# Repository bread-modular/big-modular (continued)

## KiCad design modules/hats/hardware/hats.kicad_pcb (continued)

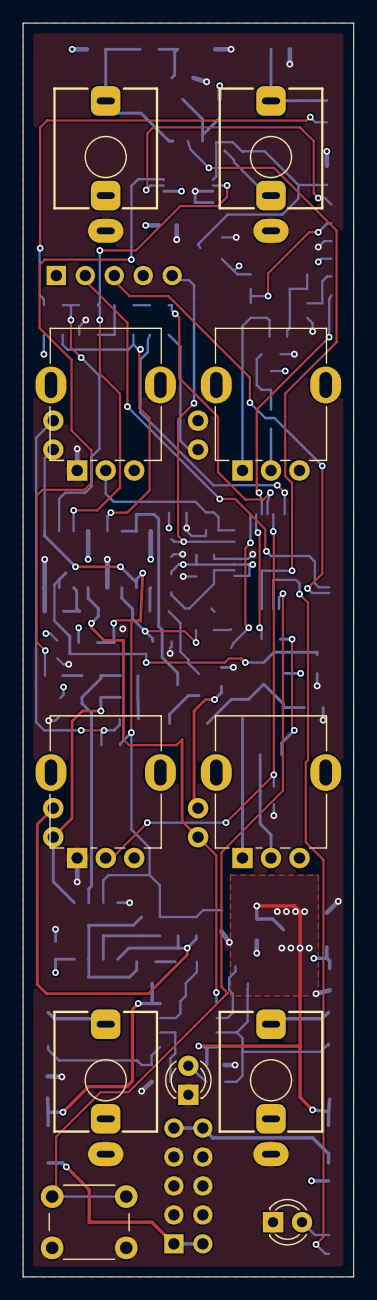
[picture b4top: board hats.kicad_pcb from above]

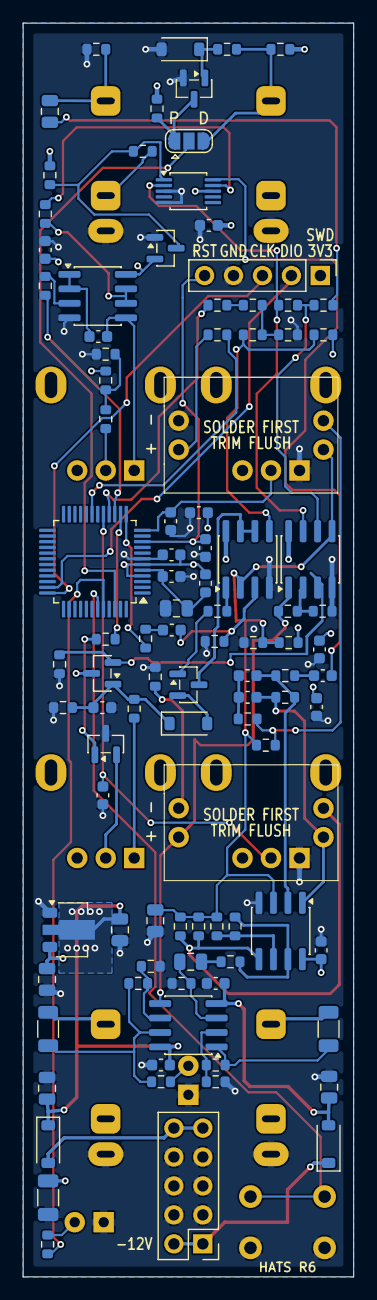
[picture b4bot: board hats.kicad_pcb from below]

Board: 4 copper layers, 29.0 x 110.0 mm, 111 parts (100 on the bottom side), 74 nets.

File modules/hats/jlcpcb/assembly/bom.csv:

Comment,Designator,Footprint,LCSC Part #,Quantity,Manufacturer,MPN
10u,"C1, C2, C4",C_0805_2012Metric,C15850,3,Samsung,CL21A106KAYNNNE
1u,"C3, C10, C21, C24",C_0805_2012Metric,C28323,4,Samsung,CL21B105KBFNNNE
100u,C5,C_1206_3216Metric,C15008,1,Samsung,CL31A107MQHNNNE
100n,"C6, C9, C11, C16, C19, C20, C22, C23, C25, C26",C_0603_1608Metric,C14663,10,YAGEO,CC0603KRX7R9BB104
4.7u,"C7, C18",C_0603_1608Metric,C19666,2,Samsung,CL10A475KO8NNNC
100p,"C8, C12",C_0603_1608Metric,C14858,2,Samsung,CL10C101JB8NNNC
1n,"C13, C14",C_0603_1608Metric,C1588,2,Samsung,CL10B102KB8NNNC
47u,C15,C_0805_2012Metric,C16780,1,Samsung,CL21A476MQYNNNE
10n,"C17, C27, C28",C_0603_1608Metric,C57112,3,FH (Guangdong Fenghua),0603B103K500NT
B5819W,"D1, D2, D4",D_SOD-123,C8598,3,CJ (Jiangsu Changjing),B5819W SL
1N4148W,D3,D_SOD-123,C81598,1,ST(Semtech),1N4148W
BAV199,D7,SOT-23,C40919,1,Nexperia,"BAV199,215"
600R@100MHz,FB1,L_0603_1608Metric,C1002,1,Sunlord,GZ1608D601TF
MMBT3904,Q1,SOT-23,C20526,1,CJ (Jiangsu Changjing),MMBT3904(RANGE:100-300)
SS8050,"Q2, Q4",SOT-23,C431710,2,MDD(Microdiode Semiconductor),SS8050
SS8550,Q3,SOT-23,C364314,1,MDD(Microdiode Semiconductor),SS8550
100k,"R1, R11, R12, R15, R27, R30, R31, R38, R39, R40, R45",R_0603_1608Metric,C25803,11,UNI-ROYAL,0603WAF1003T5E
10k,"R2, R21, R26, R29, R37, R42",R_0603_1608Metric,C25804,6,UNI-ROYAL,0603WAF1002T5E
22k,"R3, R20, R34, R49",R_0603_1608Metric,C31850,4,UNI-ROYAL,0603WAF2202T5E
1k,"R6, R8, R9, R10, R17, R22, R24, R25, R47, R48",R_0603_1608Metric,C21190,10,UNI-ROYAL,0603WAF1001T5E
330,"R7, R18, R19, R23, R28, R35, R51",R_0603_1608Metric,C23138,7,UNI-ROYAL,0603WAF3300T5E
33k,R13,R_0603_1608Metric,C4216,1,UNI-ROYAL,0603WAF3302T5E
470k,R14,R_0603_1608Metric,C23178,1,UNI-ROYAL,0603WAF4703T5E
200k,"R16, R36",R_0603_1608Metric,C25811,2,UNI-ROYAL,0603WAF2003T5E
1M,"R32, R33",R_0603_1608Metric,C22935,2,UNI-ROYAL,0603WAF1004T5E
20k,R41,R_0603_1608Metric,C4184,1,UNI-ROYAL,0603WAF2002T5E
1k,"R43, R46",R_1206_3216Metric,C2074262,2,ROHM,ESR18EZPF1001
51k,"R44, R50",R_0603_1608Metric,C23196,2,UNI-ROYAL,0603WAF5102T5E
HT7533-1,U1,SOT-89-3,C14289,1,Holtek,HT7533-1
STM32G071C8T6,U2,LQFP-48_7x7mm_P0.5mm,C529341,1,STMicroelectronics,STM32G071C8T6
MCP6002,"U4, U6, U8, U9",SOIC-8_3.9x4.9mm_P1.27mm,C7377,4,Microchip,MCP6002T-I/SN
TS5A23157,U5,TSSOP-10_3x3mm_P0.5mm,C11133,1,Texas Instruments,TS5A23157DGSR
TL072,U10,SOIC-8_3.9x4.9mm_P1.27mm,C6961,1,STMicroelectronics,TL072CDT

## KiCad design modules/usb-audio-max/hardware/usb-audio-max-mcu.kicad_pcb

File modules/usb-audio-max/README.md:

# USB-AUDIO-MAX — 6 in / 8 out USB audio interface, 96 kHz, DC coupled

A Eurorack USB audio interface: a CH32V307 (USB 2.0 High-Speed, USB Audio Class 2) and a TI
PCM3168A 24-bit codec in TDM mode. Six inputs and eight outputs, all DC coupled at about +/-5.9 V,
so CV works too. No level controls. Same two-board build as [USB-AUDIO](../usb-audio/README.md).

| Panel | Circuit |
|---|---|
| **USB** (USB-C through the panel) | MCU board: CH32V307RCT6, USBLC6-2SC6, data only (powered from the rack) |
| **IN 1-6** | 100k -> inverting driver on +5 V (x -0.24) -> PCM3168A VIN+ (single-ended); +/-5.89 V = full scale |
| **OUT 1-8** | PCM3168A VOUT+/- -> difference amplifier on +/-12 V (x 1.467) -> 1k; full scale +/-5.87 V |
| (DC reference) | +5 V analog = the codec's full-scale reference: REF5050 (8 ppm/C) -> LM358 + BCP56 discrete regulator (current-limited), so calibrated CV levels don't drift |
| (+3.3 V digital) | TPS562208 buck in forced-continuous mode (~580 kHz at every load, never in the audio band) behind a 2.2R + ferrite input filter, molded inductor; only the digital rail switches (+12 V ~0.34 A max). ngspice: ~50 uV on +12 V, 0.1 uV on +5 V analog, -142 dBFS at the jacks for USB load bursts |

**Status: S2 schematics + R1 routing on both boards, fab-review fixes done (2026-11-08), JLCPCB
export in `jlcpcb/` (not supplier-accepted, not built).** 10HP panel: USB-C at the top, then IN 1-6 in
two rows of three and OUT 1-8 in three rows (the ninth spot, bottom right, is empty; the power header sits
behind it). Both boards: native ERC 0, DRC 0 (saved fills too), unconnected 0, parity 0. Ten R/C
placements are JLCPCB Extended (user decision open, `jlcpcb/README.md`); no firmware yet (96 kHz SPI1
path untested). JLC stocks the PCM3168APAPR (C529289, Extended, 1517 on 2026-11-08).

| Path | Contents |
|---|---|
| `hardware/` | `usb-audio-max.kicad_{pro,sch,pcb}` (carrier), `usb-audio-max-mcu.kicad_{pro,sch,pcb}` (MCU board), shared `USBAUDIOMAX.kicad_sym`, `USBAUDIOMAX.pretty` (+ `PROVENANCE.json`), `USBAUDIOMAX.3dshapes`, vendored 3D models `_kicad_models/` |
| `jlcpcb/` | JLCPCB sets: `main/` (carrier Gerbers + bottom BOM/CPL, panel Gerbers), `mcu/` (MCU board Gerbers + top BOM/CPL); upload map and parts audit in `jlcpcb/README.md` |
| `panels/front-pcb/` | 10HP FR4 panel `usb-audio-max-panel.kicad_{pro,pcb}` (NPTH holes, USB-C slot, labels) |
| `docs/research.md` | Brief, decisions, levels, buck-vs-audio simulation, circuit, TDM/firmware notes, panel and fit study, sourcing, open items |
| `docs/geometry.json` | Placement and stack contract (panel frame) |
| `docs/*-schematic.pdf`, `docs/erc/`, `docs/fit/` | Schematic PDFs, native ERC JSON, native DRC JSON and placement renders |
| `tools/` | Generators (`circuit_carrier.py`, `circuit_mcu.py` hold the circuits; `build_layout.py` the S1 boards), checks, `kicad-project*.json` profiles |

Rebuild (from `modules/usb-audio-max`):

```sh
python3 -B tools/import_footprints.py   # footprint library (pcbnew); reads the Bread Modular AudioJacks/K2
python3 -B tools/build_schematic.py     # both schematics + pinned symbols, netlists asserted
python3 -B tools/build_project.py       # .kicad_pro files (only before hand edits)
python3 -B tools/build_layout.py        # S1 boards + panel (only before hand placement starts)
python3 -B tools/check_edges.py         # courtyards >= 1 mm from the edges, SMD >= 2 mm from jack pads
python3 -B tools/fit_density.py         # fit study (docs/research.md section 5)
python3 -B tools/render_fit.py          # docs/fit/*.png
kicad-cli sch erc --severity-all --format json -o docs/erc/carrier-erc.json hardware/usb-audio-max.kicad_sch
kicad-cli sch erc --severity-all --format json -o docs/erc/mcu-erc.json hardware/usb-audio-max-mcu.kicad_sch
kicad-cli pcb drc --severity-all --schematic-parity --refill-zones --format json -o docs/fit/carrier-drc.json hardware/usb-audio-max.kicad_pcb
kicad-cli pcb drc --severity-all --schematic-parity --refill-zones --format json -o docs/fit/mcu-drc.json hardware/usb-audio-max-mcu.kicad_pcb
```

Shared gate (from the repository root): `python3 -B opt/kicad-tools/kicad_tools.py check --config
modules/usb-audio-max/tools/kicad-project.json --reports <new-dir>` (and `kicad-project-mcu.json`).

Read [`Code.md`](Code.md) before changing hardware.

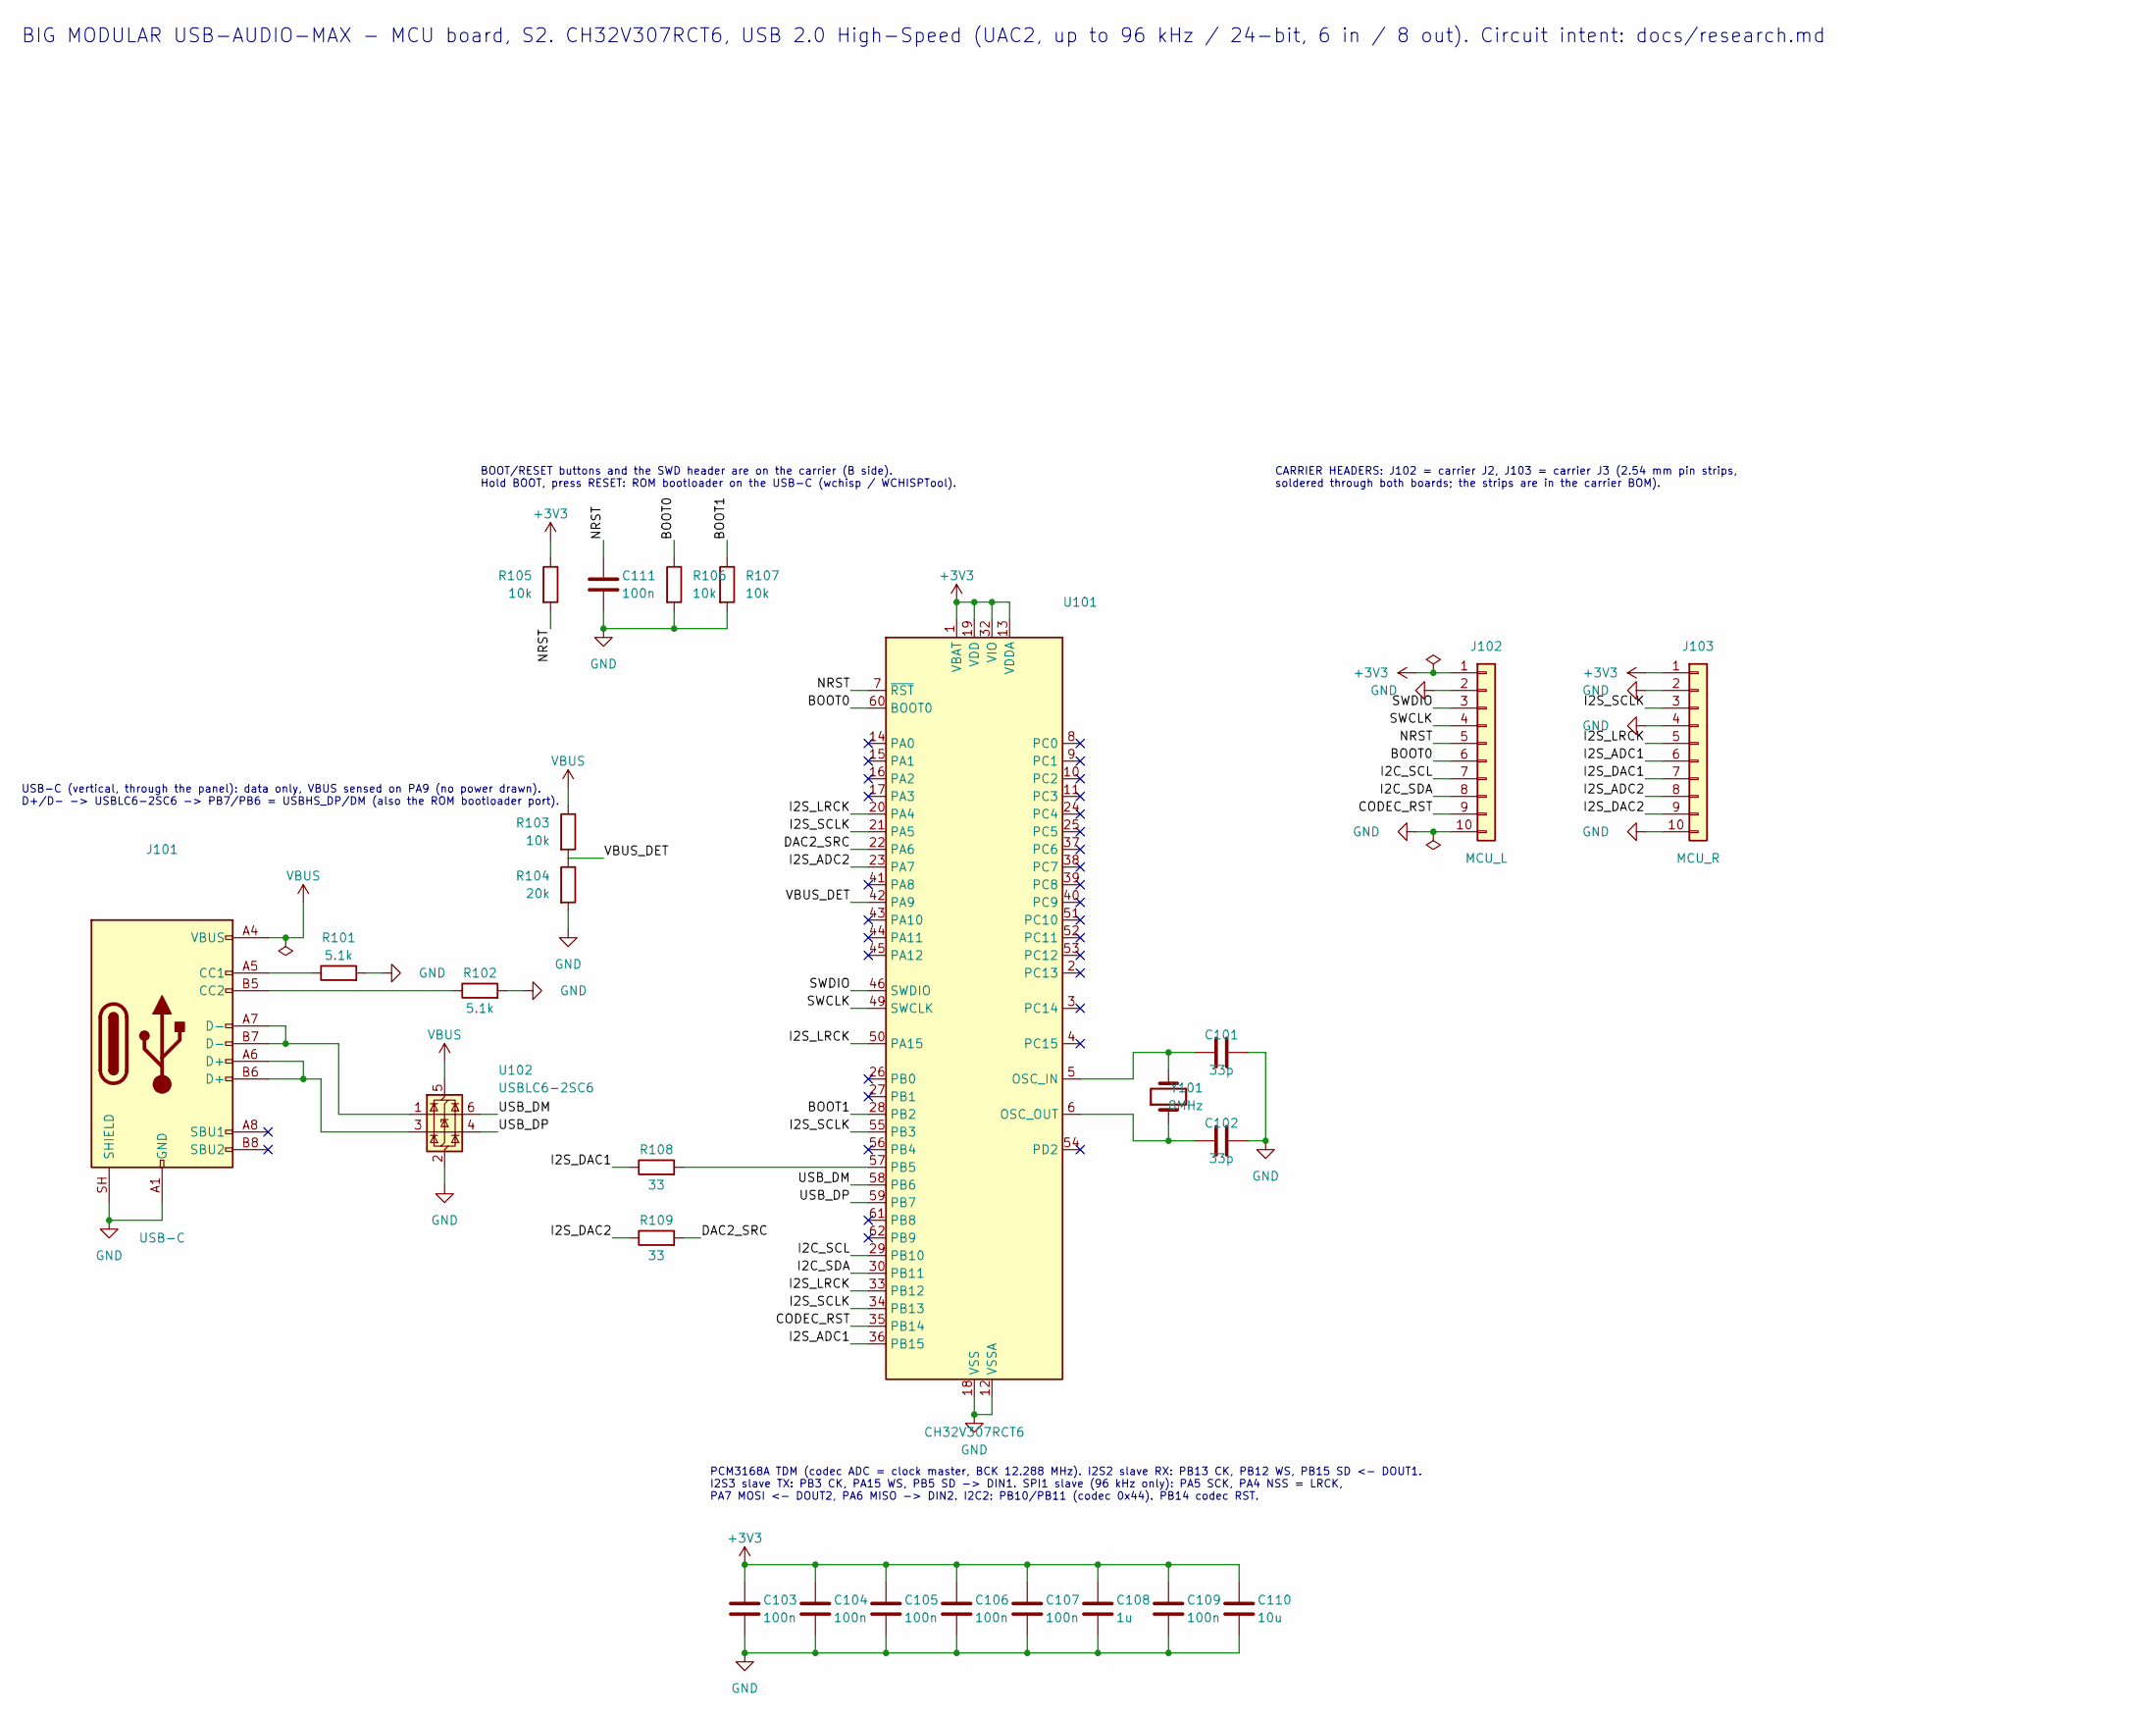
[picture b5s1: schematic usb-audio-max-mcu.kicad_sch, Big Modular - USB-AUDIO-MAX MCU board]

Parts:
C101, C102: 33p; C_0402_1005Metric; Voltage 50V; MPN 0402CG330J500NT; LCSC C1562
C103, C104, C105, C106, C107, C109, C111: 100n; C_0402_1005Metric; Voltage 16V; MPN CL05B104KO5NNNC; LCSC C1525
C108: 1u; C_0402_1005Metric; Voltage 25V; MPN CL05A105KA5NQNC; LCSC C52923
C110: 10u; C_0603_1608Metric; Voltage 10V; MPN CL10A106KP8NNNC; LCSC C19702
J101: USB-C; USB_C_Receptacle_HRO_TYPE-C-31-D-15_Vertical; MPN TYPE-C-31-D-15; LCSC C22464480
J102: MCU_L; PinHeader_1x10_P2.54mm_Vertical
J103: MCU_R; PinHeader_1x10_P2.54mm_Vertical
R101, R102: 5.1k; R_0402_1005Metric; MPN 0402WGF5101TCE; LCSC C25905
R103, R105, R106, R107: 10k; R_0402_1005Metric; MPN 0402WGF1002TCE; LCSC C25744
R104: 20k; R_0402_1005Metric; MPN 0402WGF2002TCE; LCSC C25765
R108, R109: 33; R_0402_1005Metric; MPN 0402WGF330JTCE; LCSC C25105
U101: CH32V307RCT6; LQFP-64_10x10mm_P0.5mm; MPN CH32V307RCT6; LCSC C2988083
U102: USBLC6-2SC6; SOT-23-6; MPN USBLC6-2SC6; LCSC C7519
Y101: 8MHz; Crystal_SMD_5032-2Pin_5.0x3.2mm; MPN X50328MSB2GI; LCSC C115962

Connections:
+3V3: C103.1, C104.1, C105.1, C106.1, C107.1, C108.1, C109.1, C110.1, J102.1, J103.1, R105.1, U101.1 (VBAT), U101.13 (VDDA), U101.19 (VDD), U101.32 (VIO), U101.48 (VDD), U101.64 (VIO)
/BOOT0: J102.6, R106.1, U101.60 (BOOT0)
/BOOT1: R107.1, U101.28 (PB2)
/CODEC_RST: J102.9, U101.35 (PB14)
/DAC2_SRC: R109.2, U101.22 (PA6)
/I2C_SCL: J102.7, U101.29 (PB10)
/I2C_SDA: J102.8, U101.30 (PB11)
/I2S_ADC1: J103.6, U101.36 (PB15)
/I2S_ADC2: J103.8, U101.23 (PA7)
/I2S_DAC1: J103.7, R108.1
/I2S_DAC2: J103.9, R109.1
/I2S_LRCK: J103.5, U101.20 (PA4), U101.33 (PB12), U101.50 (PA15)
/I2S_SCLK: J103.3, U101.21 (PA5), U101.34 (PB13), U101.55 (PB3)
/NRST: C111.1, J102.5, R105.2, U101.7 (~RST)
/SWCLK: J102.4, U101.49 (SWCLK)
/SWDIO: J102.3, U101.46 (SWDIO)
/USB_DM: U101.58 (PB6), U102.6 (I/O1)
/USB_DP: U101.59 (PB7), U102.4 (I/O2)
/VBUS_DET: R103.2, R104.1, U101.42 (PA9)
GND: C101.2, C102.2, C103.2, C104.2, C105.2, C106.2, C107.2, C108.2, C109.2, C110.2, C111.2, J101.A1 (GND), J101.A12 (GND), J101.B1 (GND), J101.B12 (GND), J101.SH (SHIELD), J102.2, J102.10, J103.2, J103.4, J103.10, R101.2, R102.2, R104.2, R106.2, R107.2, U101.12 (VSSA), U101.18 (VSS), U101.31 (VSS), U101.47 (VSS), U101.63 (VSS), U102.2 (GND)
unnamed: J101.A5 (CC1), R101.1
unnamed: J101.B5 (CC2), R102.1
unnamed: J101.A6 (D+), J101.B6 (D+), U102.3 (I/O2)
unnamed: J101.A7 (D-), J101.B7 (D-), U102.1 (I/O1)
unnamed: C101.1, U101.5 (OSC_IN), Y101.2
unnamed: C102.1, U101.6 (OSC_OUT), Y101.1
unnamed: R108.2, U101.57 (PB5)
VBUS: J101.A4 (VBUS), J101.A9 (VBUS), J101.B4 (VBUS), J101.B9 (VBUS), R103.1, U102.5 (VBUS)

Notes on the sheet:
CARRIER HEADERS: J102 = carrier J2, J103 = carrier J3 (2.54 mm pin strips, soldered through both boards; the strips are in the carrier BOM).
BOOT/RESET buttons and the SWD header are on the carrier (B side). Hold BOOT, press RESET: ROM bootloader on the USB-C (wchisp / WCHISPTool).
PCM3168A TDM (codec ADC = clock master, BCK 12.288 MHz). I2S2 slave RX: PB13 CK, PB12 WS, PB15 SD <- DOUT1. I2S3 slave TX: PB3 CK, PA15 WS, PB5 SD -> DIN1. SPI1 slave (96 kHz only): PA5 SCK, PA4 NSS = LRCK, PA7 MOSI <- DOUT2, PA6 MISO -> DIN2. I2C2: PB10/PB11 (codec 0x44). PB14 codec RST.
BIG MODULAR USB-AUDIO-MAX - MCU board, S2. CH32V307RCT6, USB 2.0 High-Speed (UAC2, up to 96 kHz / 24-bit, 6 in / 8 out). Circuit intent: docs/research.md
USB-C (vertical, through the panel): data only, VBUS sensed on PA9 (no power drawn). D+/D- -> USBLC6-2SC6 -> PB7/PB6 = USBHS_DP/DM (also the ROM bootloader port).

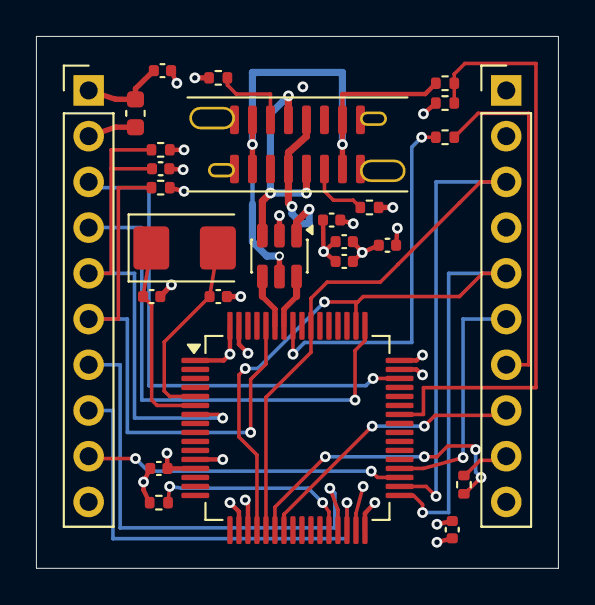
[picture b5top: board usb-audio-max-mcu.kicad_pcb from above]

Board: 4 copper layers, 29.0 x 29.5 mm, 26 parts (0 on the bottom side), 28 nets.

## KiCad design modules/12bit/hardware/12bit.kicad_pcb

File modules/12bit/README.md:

# 12bit — STM32G071 two-channel DAC voice (6HP)

modules/8bit moved from the ATtiny1616 to an **STM32G071C8T6**: its two 12-bit DAC channels
drive two outputs and the passive low-pass is gone (knob 3 is a plain knob). 6HP. (The S1
gate output was removed in S2.)

| Panel (top to bottom) | Circuit |
|---|---|
| **MIDI** in (TS) / **CV** in | 8bit MIDI V2 NPN front end, JP1 on the back (shipped open): `P` = protected (USART1 RX inverted in firmware), `D` = direct. CV: -5.9..+6.0 V -> 0..3.3 V (Zin 138k), BAT54SW clamp, MCP6001 follower into PA0; unpatched = 0 V |
| **P1**, **P2** / **MODE**, LED, **P3** | 50k linear RV09 dividers into PA1 / PA6 / PA7. MODE: 8bit 6 x 6 x 7 mm THT switch (PB4) with the 8bit printed cap; 3 mm LED beside it on the same row (PB5, PWM) |
| **OUT 1**, **OUT 2** | DAC1_OUT1 / DAC1_OUT2 -> 1k/4.7n step smoothing (34 kHz) -> TL074 x3.4 around a 2.33 V offset -> ±4.9 V, DC coupled (audio, CV or LFO), 1k 0.5 W |

Power: Eurorack 10-pin (16-pin IDC fits) on B, upright at the right edge above OUT 2, ±12 V through series
Schottkys, +3V3 from an HT7533-1. SWD on a 1x5 header on B (1 3V3 sense, 2 SWDIO, 3 SWCLK,
4 GND, 5 NRST).

**Status: S2 schematic (ERC 0) + P3 placement + R2 2-layer hand routing (DRC 0, unconnected 0,
parity 0) + JLCPCB export in `jlcpcb/` (not supplier-accepted).** No firmware. See `docs/research.md` for decisions and open items.

| Path | Contents |
|---|---|
| `hardware/` | KiCad project `12bit.kicad_{pro,sch,pcb}` (29 x 110 mm carrier, 2 layers, routed R2), pinned symbols/footprints/models |
| `panels/front-pcb/12bit-panel.kicad_{pro,pcb}` | 6HP FR4 front panel: NPTH only, silkscreen labels |
| `docs/research.md` | Brief, decisions, circuit, placement, open items |
| `docs/geometry.json` | Placement contract (panel frame) |
| `docs/12bit-schematic.pdf`, `docs/fit/` | Schematic PDF; native ERC/DRC JSON and renders |
| `docs/schematic-symbols.json`, `docs/sourcing-candidates.json` | Pinned-symbol provenance; dated live JLCPCB lookups |
| `tools/` | Generators and the shared-tool profile `kicad-project.json` |

Rebuild (from `modules/12bit`; the carrier is now routed, so `build_layout.py` refuses it; use `--panel-only` for the panel):

```sh
python3 -B tools/import_footprints.py   # one-time library import (pcbnew)
python3 -B tools/build_schematic.py     # schematic + pinned symbols, netlist asserted
python3 -B tools/build_layout.py        # THT placement + parked SMD + nets, UNROUTED; panel
(cd ../.. && python3 -B opt/kicad-tools/kicad_tools.py check --config modules/12bit/tools/kicad-project.json \
   --reports modules/12bit/research/check-NEW)
```

Read [`Code.md`](Code.md) before changing hardware.

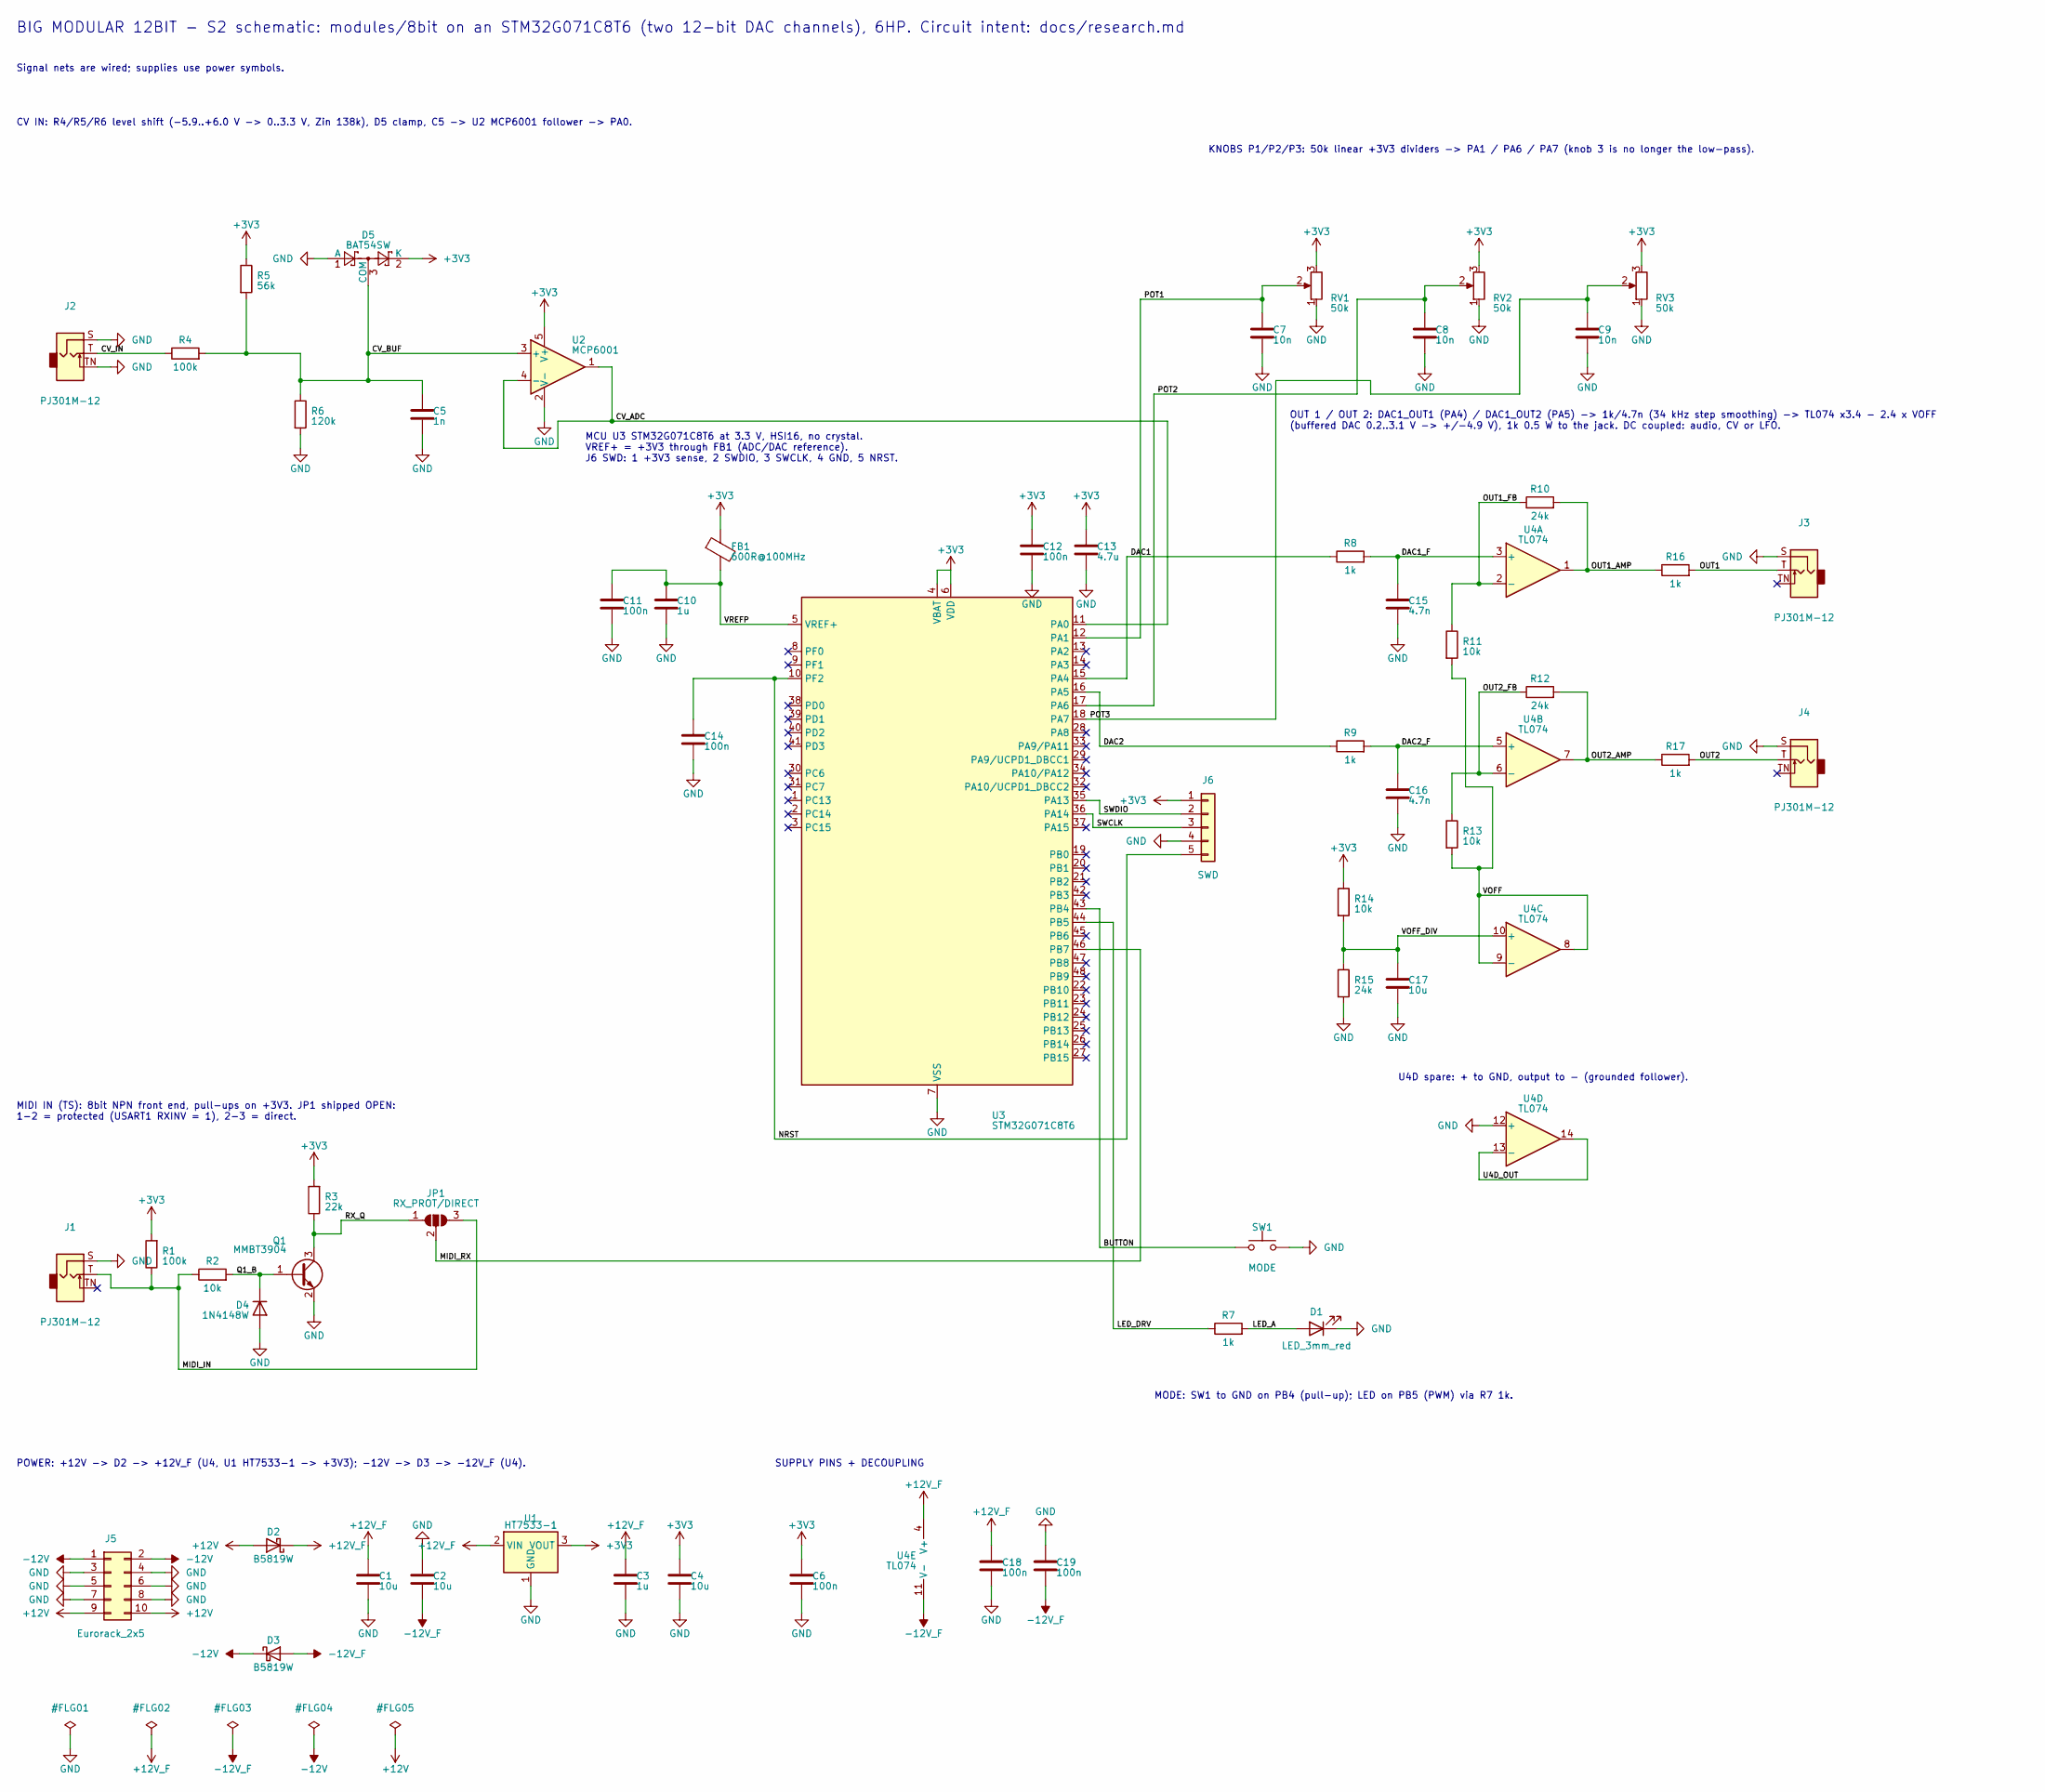
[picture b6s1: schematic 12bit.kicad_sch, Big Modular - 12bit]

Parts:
C1, C2, C4, C17: 10u; C_0805_2012Metric; Voltage 25V; MPN CL21A106KAYNNNE; LCSC C15850
C3, C10: 1u; C_0805_2012Metric; Voltage 50V; MPN CL21B105KBFNNNE; LCSC C28323
C5: 1n; C_0603_1608Metric; Voltage 50V; MPN CL10B102KB8NNNC; LCSC C1588
C6, C11, C12, C14, C18, C19: 100n; C_0603_1608Metric; Voltage 50V; MPN CC0603KRX7R9BB104; LCSC C14663
C7, C8, C9: 10n; C_0603_1608Metric; Voltage 50V; MPN 0603B103K500NT; LCSC C57112
C13: 4.7u; C_0603_1608Metric; Voltage 16V; MPN CL10A475KO8NNNC; LCSC C19666
C15, C16: 4.7n; C_0603_1608Metric; Voltage 50V; MPN 0603B472K500NT; LCSC C53987
D1: LED_3mm_red; LED_D3.0mm
D2, D3: B5819W; D_SOD-123; MPN B5819W SL; LCSC C8598
D4: 1N4148W; D_SOD-123; MPN 1N4148W; LCSC C81598
D5: BAT54SW; SOT-323_SC-70; MPN BAT54SWT1G; LCSC C78260
FB1: 600R@100MHz; L_0603_1608Metric; MPN GZ1608D601TF; LCSC C1002
J1, J2, J3, J4: PJ301M-12; Jack_3.5mm_QingPu_WQP-PJ301M-12_Vertical
J5: Eurorack_2x5; PinHeader_2x05_P2.54mm_Vertical
J6: SWD; PinHeader_1x05_P2.54mm_Vertical
JP1: RX_PROT/DIRECT; SolderJumper-3_P1.3mm_Open_RoundedPad1.0x1.5mm
Q1: MMBT3904; SOT-23; MPN MMBT3904(RANGE:100-300); LCSC C20526
R1, R4: 100k; R_0603_1608Metric; MPN 0603WAF1003T5E; LCSC C25803
R2, R11, R13, R14: 10k; R_0603_1608Metric; MPN 0603WAF1002T5E; LCSC C25804
R3: 22k; R_0603_1608Metric; MPN 0603WAF2202T5E; LCSC C31850
R5: 56k; R_0603_1608Metric; MPN 0603WAF5602T5E; LCSC C23206
R6: 120k; R_0603_1608Metric; MPN 0603WAF1203T5E; LCSC C25808
R7, R8, R9: 1k; R_0603_1608Metric; MPN 0603WAF1001T5E; LCSC C21190
R10, R12, R15: 24k; R_0603_1608Metric; MPN 0603WAF2402T5E; LCSC C23352
R16, R17: 1k; R_1206_3216Metric; MPN ESR18EZPF1001; LCSC C2074262
RV1, RV2, RV3: 50k; Potentiometer_RV09
SW1: MODE; SW_PUSH_6mm_H7.3mm; MPN 6x6x7 mm THT tact switch, 4 pins (gener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
U1: HT7533-1; SOT-89-3; MPN HT7533-1; LCSC C14289
U2: MCP6001; SOT-23-5; MPN MCP6001T-E/OT; LCSC C29429
U3: STM32G071C8T6; LQFP-48_7x7mm_P0.5mm; MPN STM32G071C8T6; LCSC C529341
U4: TL074; SOIC-14_3.9x8.7mm_P1.27mm; MPN TL074CDR; LCSC C12594

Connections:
+3V3: C4.1, C6.1, C12.1, C13.1, D5.2 (K), FB1.1, J6.1, R1.2, R3.2, R5.1, R14.1, RV1.3, RV2.3, RV3.3, U1.3 (VOUT), U2.5 (V+), U3.4 (VBAT), U3.6 (VDD)
+12V: D2.2 (A), J5.9, J5.10
+12V_F: C1.1, C3.1, C18.1, D2.1 (K), U1.2 (VIN), U4.4 (V+)
-12V: D3.1 (K), J5.1, J5.2
-12V_F: C2.2, C19.2, D3.2 (A), U4.11 (V-)
/BUTTON: SW1.1, U3.43 (PB4)
/CV_ADC: U2.1, U2.4 (-), U3.11 (PA0)
/CV_BUF: C5.1, D5.3 (COM), R4.2, R5.2, R6.1, U2.3 (+)
/CV_IN: J2.T, R4.1
/DAC1: R8.1, U3.15 (PA4)
/DAC1_F: C15.1, R8.2, U4.3 (+)
/DAC2: R9.1, U3.16 (PA5)
/DAC2_F: C16.1, R9.2, U4.5 (+)
/LED_A: D1.2 (A), R7.2
/LED_DRV: R7.1, U3.44 (PB5)
/MIDI_IN: J1.T, JP1.3 (B), R1.1, R2.1
/MIDI_RX: JP1.2 (C), U3.46 (PB7)
/NRST: C14.1, J6.5, U3.10 (PF2)
/OUT1: J3.T, R16.2
/OUT1_AMP: R10.2, R16.1, U4.1
/OUT1_FB: R10.1, R11.1, U4.2 (-)
/OUT2: J4.T, R17.2
/OUT2_AMP: R12.2, R17.1, U4.7
/OUT2_FB: R12.1, R13.1, U4.6 (-)
/POT1: C7.1, RV1.2, U3.12 (PA1)
/POT2: C8.1, RV2.2, U3.17 (PA6)
/POT3: C9.1, RV3.2, U3.18 (PA7)
/Q1_B: D4.1 (K), Q1.1 (B), R2.2
/RX_Q: JP1.1 (A), Q1.3 (C), R3.1
/SWCLK: J6.3, U3.36 (PA14)
/SWDIO: J6.2, U3.35 (PA13)
/U4D_OUT: U4.13 (-), U4.14
/VOFF: R11.2, R13.2, U4.8, U4.9 (-)
/VOFF_DIV: C17.1, R14.2, R15.1, U4.10 (+)
/VREFP: C10.1, C11.1, FB1.2, U3.5 (VREF+)
GND: C1.2, C2.1, C3.2, C4.2, C5.2, C6.2, C7.2, C8.2, C9.2, C10.2, C11.2, C12.2, C13.2, C14.2, C15.2, C16.2, C17.2, C18.2, C19.1, D1.1 (K), D4.2 (A), D5.1 (A), J1.S, J2.S, J2.TN, J3.S, J4.S, J5.3, J5.4, J5.5, J5.6, J5.7, J5.8, J6.4, Q1.2 (E), R6.2, R15.2, RV1.1, RV2.1, RV3.1, SW1.2, U1.1 (GND), U2.2 (V-), U3.7 (VSS), U4.12 (+)

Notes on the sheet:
SUPPLY PINS + DECOUPLING
CV IN: R4/R5/R6 level shift (-5.9..+6.0 V -> 0..3.3 V, Zin 138k), D5 clamp, C5 -> U2 MCP6001 follower -> PA0.
U4D spare: + to GND, output to - (grounded follower).
Signal nets are wired; supplies use power symbols.
MCU U3 STM32G071C8T6 at 3.3 V, HSI16, no crystal. VREF+ = +3V3 through FB1 (ADC/DAC reference). J6 SWD: 1 +3V3 sense, 2 SWDIO, 3 SWCLK, 4 GND, 5 NRST.
MODE: SW1 to GND on PB4 (pull-up); LED on PB5 (PWM) via R7 1k.
MIDI IN (TS): 8bit NPN front end, pull-ups on +3V3. JP1 shipped OPEN: 1-2 = protected (USART1 RXINV = 1), 2-3 = direct.
BIG MODULAR 12BIT - S2 schematic: modules/8bit on an STM32G071C8T6 (two 12-bit DAC channels), 6HP. Circuit intent: docs/research.md
KNOBS P1/P2/P3: 50k linear +3V3 dividers -> PA1 / PA6 / PA7 (knob 3 is no longer the low-pass).
OUT 1 / OUT 2: DAC1_OUT1 (PA4) / DAC1_OUT2 (PA5) -> 1k/4.7n (34 kHz step smoothing) -> TL074 x3.4 - 2.4 x VOFF (buffered DAC 0.2..3.1 V -> +/-4.9 V), 1k 0.5 W to the jack. DC coupled: audio, CV or LFO.
POWER: +12V -> D2 -> +12V_F (U4, U1 HT7533-1 -> +3V3); -12V -> D3 -> -12V_F (U4).

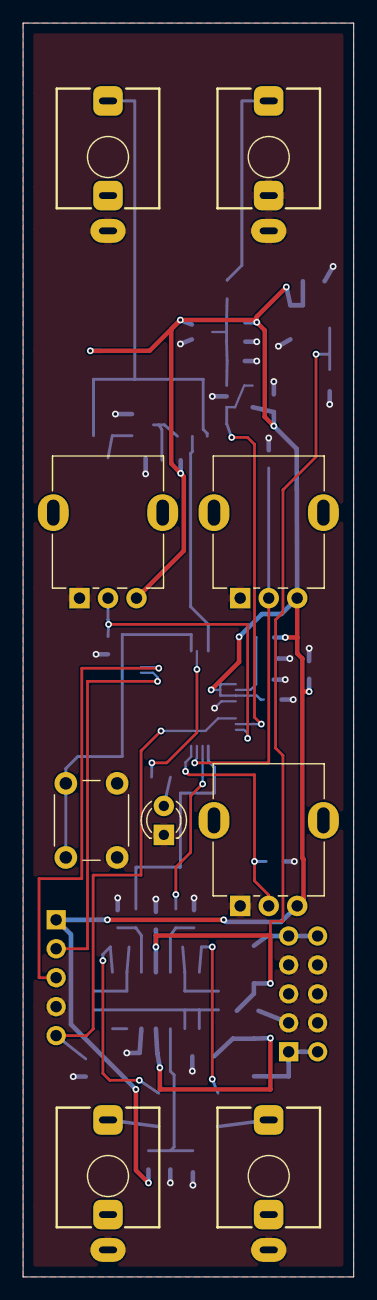
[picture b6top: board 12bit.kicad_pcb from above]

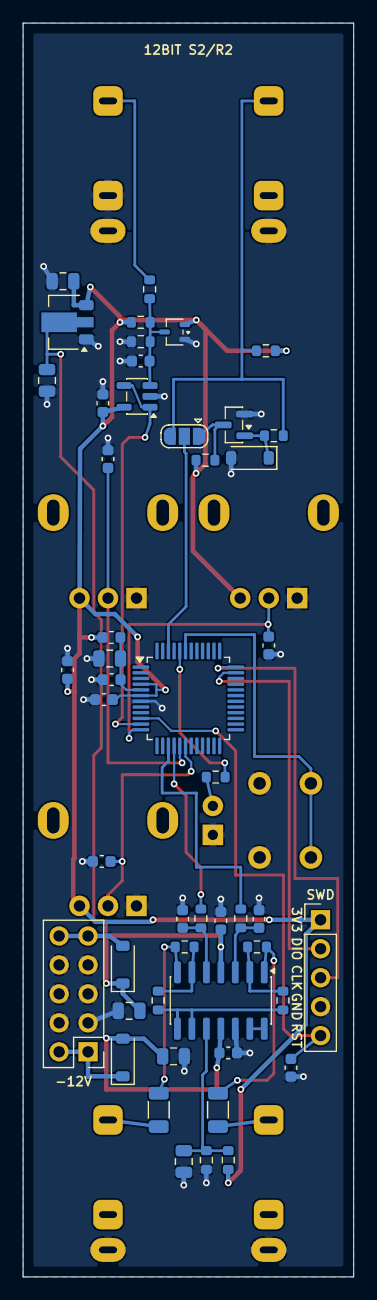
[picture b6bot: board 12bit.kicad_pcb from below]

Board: 2 copper layers, 29.0 x 110.0 mm, 58 parts (49 on the bottom side), 36 nets.

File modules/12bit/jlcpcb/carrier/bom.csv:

Comment,Designator,Footprint,LCSC Part #,Quantity,Manufacturer,MPN
10u,"C1, C2, C4, C17",C_0805_2012Metric,C15850,4,Samsung,CL21A106KAYNNNE
1u,"C3, C10",C_0805_2012Metric,C28323,2,Samsung,CL21B105KBFNNNE
1n,C5,C_0603_1608Metric,C1588,1,Samsung,CL10B102KB8NNNC
100n,"C6, C11, C12, C14, C18, C19",C_0603_1608Metric,C14663,6,YAGEO,CC0603KRX7R9BB104
10n,"C7, C8, C9",C_0603_1608Metric,C57112,3,FH (Guangdong Fenghua),0603B103K500NT
4.7u,C13,C_0603_1608Metric,C19666,1,Samsung,CL10A475KO8NNNC
4.7n,"C15, C16",C_0603_1608Metric,C53987,2,FH (Guangdong Fenghua),0603B472K500NT
B5819W,"D2, D3",D_SOD-123,C8598,2,CJ (Jiangsu Changjing),B5819W SL
1N4148W,D4,D_SOD-123,C81598,1,ST(Semtech),1N4148W
BAT54SW,D5,SOT-323_SC-70,C78260,1,onsemi,BAT54SWT1G
600R@100MHz,FB1,L_0603_1608Metric,C1002,1,Sunlord,GZ1608D601TF
MMBT3904,Q1,SOT-23,C20526,1,CJ (Jiangsu Changjing),MMBT3904(RANGE:100-300)
100k,"R1, R4",R_0603_1608Metric,C25803,2,UNI-ROYAL,0603WAF1003T5E
10k,"R2, R11, R13, R14",R_0603_1608Metric,C25804,4,UNI-ROYAL,0603WAF1002T5E
22k,R3,R_0603_1608Metric,C31850,1,UNI-ROYAL,0603WAF2202T5E
56k,R5,R_0603_1608Metric,C23206,1,UNI-ROYAL,0603WAF5602T5E
120k,R6,R_0603_1608Metric,C25808,1,UNI-ROYAL,0603WAF1203T5E
1k,"R7, R8, R9",R_0603_1608Metric,C21190,3,UNI-ROYAL,0603WAF1001T5E
24k,"R10, R12, R15",R_0603_1608Metric,C23352,3,UNI-ROYAL,0603WAF2402T5E
1k,"R16, R17",R_1206_3216Metric,C2074262,2,ROHM,ESR18EZPF1001
HT7533-1,U1,SOT-89-3,C14289,1,Holtek,HT7533-1
MCP6001,U2,SOT-23-5,C29429,1,Microchip,MCP6001T-E/OT
STM32G071C8T6,U3,LQFP-48_7x7mm_P0.5mm,C529341,1,STMicroelectronics,STM32G071C8T6
TL074,U4,SOIC-14_3.9x8.7mm_P1.27mm,C12594,1,Texas Instruments,TL074CDR

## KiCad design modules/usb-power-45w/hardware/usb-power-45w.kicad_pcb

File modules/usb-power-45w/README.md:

# usb-power-45w

USB-C PD Eurorack supply, ±12 V only, on one 4-layer carrier behind a 4HP panel.

> **S9.3-10P / R1: routed, first-prototype fab export in [`jlcpcb/`](jlcpcb/README.md) (2026-11-06).** Not a
> supplier-accepted release and not bench-qualified. The copper/thermal screen (`tools/check_s8_board.py`) still lists
> contract items; each was reviewed and accepted for the first prototype ([fab review](docs/routing/README.md)).

## Open

| Open in KiCad | What it is |
| --- | --- |
| **[`hardware/usb-power-45w.kicad_pro`](hardware/usb-power-45w.kicad_pro)** | The module: schematic (`usb-power-45w.kicad_sch` + pages `01`..`05`) and the routed 4-layer PCB (`usb-power-45w.kicad_{pcb,dru}`) |
| [`panels/front-pcb/usb-power-45w-panel.kicad_pro`](panels/front-pcb/usb-power-45w-panel.kicad_pro) | 4HP FR4 front panel (USB-C aperture, MAIN LED, RESET, rail and bracket holes) |
| [`panels/bracket/`](panels/bracket/) | The two M3 L brackets (STEP/STL/FreeCAD) |

## Circuit

- **Input:** USB-C PD **15 V / 3 A** (CH224A, R1 56k). U5 TPS16630 main eFuse; precision UVLO (on 12.263–12.976 V,
  off 11.365–12.193 V) and OVP (R24 9.1k: 17.30–19.44 V) coordinated with the D24 SMBJ20A clamp.
- **+12 V:** TPS552892-Q1 buck-boost (U2), R109 18 mΩ RLM12 current sense on a 4-terminal Kelvin land.
- **−12 V:** LMR38020 inverting converter (U4) on its own input enable (Q1 on VPD, RUN and MAIN_LED_OK via Q14/Q15),
  sequenced after +12 V (Q16 gate = P12_OK via R118/C86).
- **Strict 3 A start (S9.3):** FB-injection soft starts on both converters (C84/D27/R116 on U2, τ 15 ms nominal;
  C85/D28/R117 on U4, τ 47 ms). Netlist plant: peak input 2.955 A, zero U5 drop-outs in all five cases.
- **Faults:** one-shot `STARTED` arming, always-on latch and RESET button; D8 MAIN is the only panel LED.
- **Output:** two 10-pin shrouded IDC headers J2/J3 (Wurth 61201021621; pins 1/2 −12 V, 3–8 GND, 9/10 +12 V).
  No series reverse blocking (owner decision).
- **Prototype targets:** +12 V 2.4 A / −12 V 0.8 A, ≤ 33 W combined, conditional on the routing contract and the
  post-prototype acceptance tests.

## Status

- Native ERC 0; DRC **0 violations, 0 warnings, 0 exclusions, 0 unconnected**; exact ref/pin/net parity
  (185 refs / 84 nets). Manual divide-and-conquer routing, In1 one-piece GND plane, two approved In2 hops.
- Routing contract enforced by native DRC: 8 net classes, 22 `S92_*` rules, 15 rule areas. **No via-in-pad**:
  U4/U5/U9 sit on hole-free lands with thermal-via fields beside the pads (standard 0.3/0.6 mm tented vias).
- All parts on F; test points on B with silkscreen labels. JLCPCB places 155 parts on the top (J1 included);
  J2/J3 (Wurth 61201021621) and D8 (3 mm LED) are hand-fitted.
- **Fab review (2026-11-06):** fixed the two DRC errors left by a KiCad 10 *Update PCB from Schematic* (the SW1
  case-pad link), added a third +12V output via at R109, a third D1 TVS ground via and a U2 PGND via, and moved
  J2/J3/D8 out of the CPL so J1 is machine-placed. D1 SMBJ22A was re-sourced to Littelfuse C224015 (1,947 in stock;
  RUILON C10214 had 59). Export: [`jlcpcb/`](jlcpcb/README.md).
- **Accepted for the first prototype, still listed by `check_s8_board.py`:** minimum widths (taps and short stubs
  only), U2/R109/D10 thermal copper (TH-1/TH-2 measure it), U12.14→C52.1 7.63 mm, D25↔D24 9.04 mm, TP22/TP23 pair
  8.25 mm, R116.1 pad edge inside RA_AGND_ISLAND; see the [fab review](docs/routing/README.md). The items in
  [routing-notes.md](docs/design/routing-notes.md) (test points, uncertainty register, routing constraints) are
  post-prototype acceptance tests, not design blockers.

## Read

- [Design and changelog](docs/design.md)
- [Manufacturing export](jlcpcb/README.md) · [Fab review and routing checkpoint](docs/routing/README.md) · [Routing log](docs/routing/continuation-238.md) · [Routing notes](docs/design/routing-notes.md)
- [Schematic PDF](docs/usb-power-45w-schematic.pdf) · [BOM](docs/design/bom.csv) · [Sourcing](docs/design/sourcing.json)
- [Calculations](docs/design/calcs.json) · [Validation](docs/design/validation.json) · [Review record](docs/design/review-s93.json)
- [Assembly PDF](docs/design/assembly/usb-power-45w-placement.pdf) · [STEP](docs/design/assembly/usb-power-45w-assembly.step.zip)
- [Capacitor study](docs/capacitor-study/README.md)

## Rebuild and check

Run from the repository root; raw reports go in the ignored `research/`. The full sequence is in
[docs/design.md](docs/design.md#reproducibility).

```sh
python3 -B modules/usb-power-45w/tools/build_s8.py --output-root <candidate-module-root>
python3 -B opt/kicad-tools/kicad_tools.py check --config modules/usb-power-45w/tools/kicad-project.json --reports <new-dir>
python3 -B -m unittest discover -s modules/usb-power-45w/tools -p 'test_*.py' -v
```

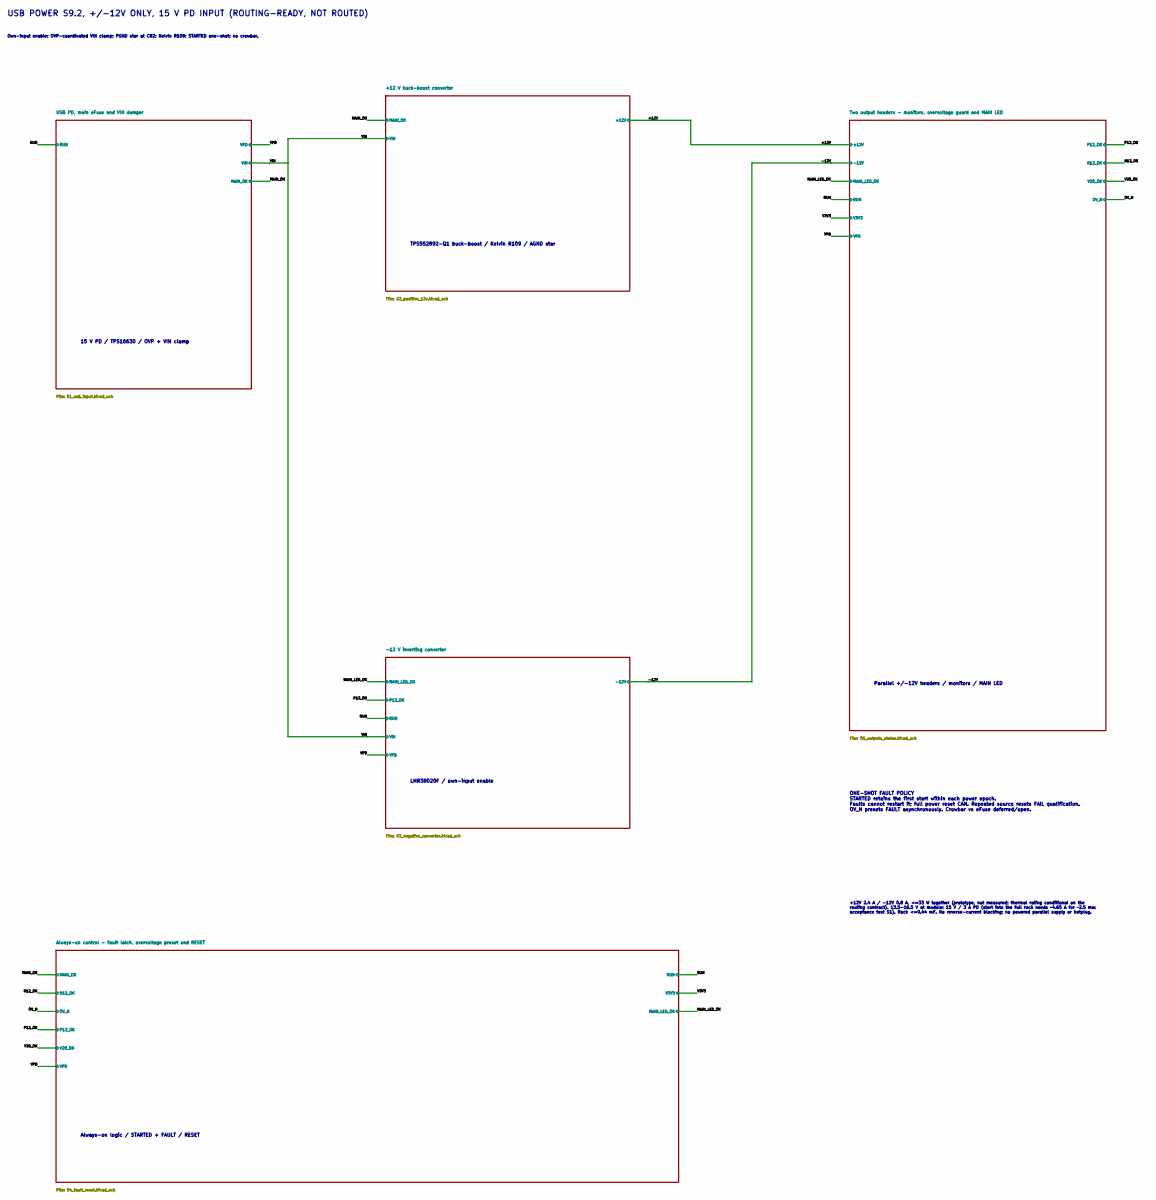
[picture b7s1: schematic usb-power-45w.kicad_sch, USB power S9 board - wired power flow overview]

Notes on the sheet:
ONE-SHOT FAULT POLICY STARTED retains the first start within each power epoch. Faults cannot restart it; full power reset CAN. Repeated source resets FAIL qualification. OV_N presets FAULT asynchronously. Crowbar vs eFuse deferred/open.
TPS552892-Q1 buck-boost / Kelvin R109 / AGND star
USB POWER S9.2, +/-12V ONLY, 15 V PD INPUT (ROUTING-READY, NOT ROUTED)
Parallel +/-12V headers / monitors / MAIN LED
LMR38020F / own-input enable
15 V PD / TPS16630 / OVP + VIN clamp
Own-input enable; OVP-coordinated VIN clamp; PGND star at C82; Kelvin R109; STARTED one-shot; no crowbar.
+12V 2.4 A / -12V 0.8 A, <=33 W together (prototype, not measured; thermal rating conditional on the routing contract). 13.5-16.5 V at module; 15 V / 3 A PD (start into the full rack needs ~4.65 A for ~2.5 ms: acceptance test S1). Rack <=0.44 mF. No reverse-current blocking; no powered parallel sup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
Always-on logic / STARTED + FAULT / RESET
